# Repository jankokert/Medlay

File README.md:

# Medlay
A modular micropower managment layout

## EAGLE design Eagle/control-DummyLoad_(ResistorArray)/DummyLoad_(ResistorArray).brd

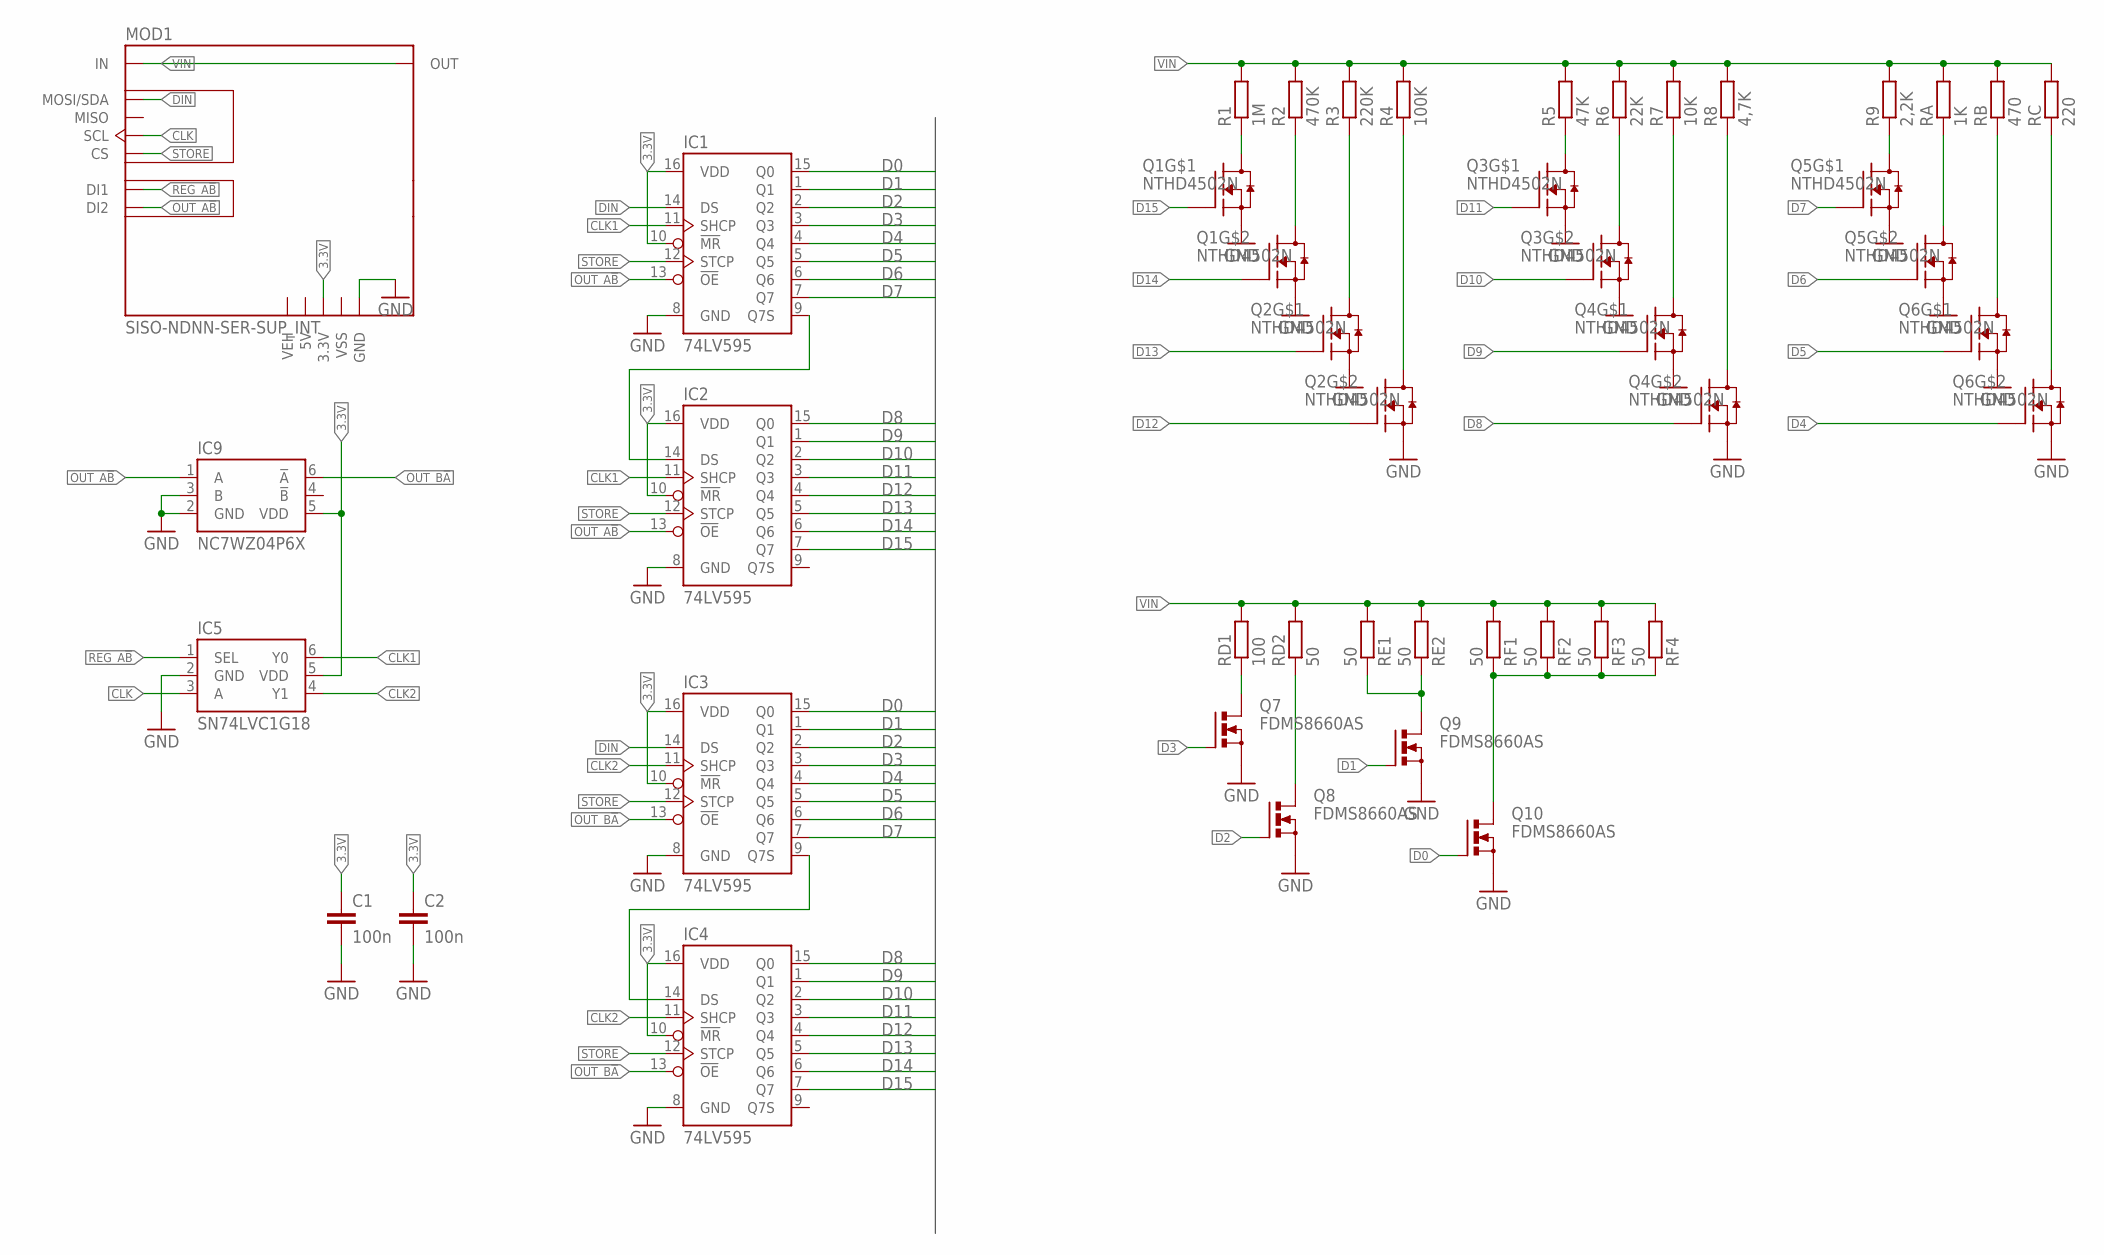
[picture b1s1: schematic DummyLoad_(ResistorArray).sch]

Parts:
C1, C2: 100n; C0805K
IC1, IC2, IC3, IC4: 74LV595; TSSOP16
IC5: SN74LVC1G18; SOT65
IC9: NC7WZ04P6X; SOT65P210X110-6N
MOD1: SISO-NDNN-SER-SUP_INT; SISO-NDNN-SER-SUP
Q1, Q2, Q3, Q4, Q5, Q6: NTHD4502N; 1206A_CHIPFET
Q7, Q8, Q9, Q10: FDMS8660AS; PG-TDSON-8
R1: 1M; R0805
R2: 470K; R0805
R3: 220K; R0805
R4: 100K; R0805
R5: 47K; R0805
R6: 22K; R0805
R7: 10K; R0805
R8: 4,7K; R0805
R9: 2,2K; R0805
RA: 1K; R0805
RB: 470; R0805
RC: 220; R0805
RD1: 100; R1206
RD2: 50; R1206
RE1, RE2: 50; R1206
RF1, RF2, RF3, RF4: 50; R1206

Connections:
3.3V: C1.1, C2.1, IC1.10 (!MR), IC1.16 (VDD), IC2.10 (!MR), IC2.16 (VDD), IC3.10 (!MR), IC3.16 (VDD), IC4.10 (!MR), IC4.16 (VDD), IC5.5 (VDD), IC9.5 (VDD), MOD1.3.3V
5V: MOD1.5V
CLK: IC5.3 (A), MOD1.SCL
CLK1: IC1.11 (SHCP), IC2.11 (SHCP), IC5.6 (Y0)
CLK2: IC3.11 (SHCP), IC4.11 (SHCP), IC5.4 (Y1)
D0: IC1.15 (Q0), IC3.15 (Q0), Q10.4 (G)
D1: IC1.1 (Q1), IC3.1 (Q1), Q9.4 (G)
D2: IC1.2 (Q2), IC3.2 (Q2), Q8.4 (G)
D3: IC1.3 (Q3), IC3.3 (Q3), Q7.4 (G)
D4: IC1.4 (Q4), IC3.4 (Q4), Q6.4 (G)
D5: IC1.5 (Q5), IC3.5 (Q5), Q6.2 (G)
D6: IC1.6 (Q6), IC3.6 (Q6), Q5.4 (G)
D7: IC1.7 (Q7), IC3.7 (Q7), Q5.2 (G)
D8: IC2.15 (Q0), IC4.15 (Q0), Q4.4 (G)
D9: IC2.1 (Q1), IC4.1 (Q1), Q4.2 (G)
D10: IC2.2 (Q2), IC4.2 (Q2), Q3.4 (G)
D11: IC2.3 (Q3), IC4.3 (Q3), Q3.2 (G)
D12: IC2.4 (Q4), IC4.4 (Q4), Q2.4 (G)
D13: IC2.5 (Q5), IC4.5 (Q5), Q2.2 (G)
D14: IC2.6 (Q6), IC4.6 (Q6), Q1.4 (G)
D15: IC2.7 (Q7), IC4.7 (Q7), Q1.2 (G)
DIN: IC1.14 (DS), IC3.14 (DS), MOD1.MOSI/SDA
GND: C1.2, C2.2, IC1.8 (GND), IC2.8 (GND), IC3.8 (GND), IC4.8 (GND), IC5.2 (GND), IC9.2 (GND), IC9.3 (B), MOD1.GND1 (GND), MOD1.GND2 (GND), MOD1.GND3 (GND), MOD1.GND4 (GND), Q1.1 (S), Q1.3 (S), Q2.1 (S), Q2.3 (S), Q3.1 (S), Q3.3 (S), Q4.1 (S), Q4.3 (S), Q5.1 (S), Q5.3 (S), Q6.1 (S), Q6.3 (S), Q7.1 (S), Q7.2 (S), Q7.3 (S), Q8.1 (S), Q8.2 (S), Q8.3 (S), Q9.1 (S), Q9.2 (S), Q9.3 (S), Q10.1 (S), Q10.2 (S), Q10.3 (S)
unnamed: Q7.5 (D), Q7.6 (D), Q7.7 (D), Q7.8 (D), Q7.TH (D), RD1.1
unnamed: Q1.7 (D), Q1.8 (D), R1.1
unnamed: IC1.9 (Q7S), IC2.14 (DS)
unnamed: IC3.9 (Q7S), IC4.14 (DS)
unnamed: Q5.7 (D), Q5.8 (D), R9.1
unnamed: Q5.5 (D), Q5.6 (D), RA.1
unnamed: Q6.7 (D), Q6.8 (D), RB.1
unnamed: Q6.5 (D), Q6.6 (D), RC.1
unnamed: Q1.5 (D), Q1.6 (D), R2.1
unnamed: Q2.7 (D), Q2.8 (D), R3.1
unnamed: Q8.5 (D), Q8.6 (D), Q8.7 (D), Q8.8 (D), Q8.TH (D), RD2.1
unnamed: Q2.5 (D), Q2.6 (D), R4.1
unnamed: Q3.7 (D), Q3.8 (D), R5.1
unnamed: Q9.5 (D), Q9.6 (D), Q9.7 (D), Q9.8 (D), Q9.TH (D), RE1.1, RE2.1
unnamed: Q3.5 (D), Q3.6 (D), R6.1
unnamed: Q4.7 (D), Q4.8 (D), R7.1
unnamed: Q4.5 (D), Q4.6 (D), R8.1
unnamed: Q10.5 (D), Q10.6 (D), Q10.7 (D), Q10.8 (D), Q10.TH (D), RF1.1, RF2.1, RF3.1, RF4.1
OUT_A!B: IC1.13 (!OE), IC2.13 (!OE), IC9.1 (A), MOD1.DI2
OUT_B!A: IC3.13 (!OE), IC4.13 (!OE), IC9.6 (!A)
REG_A!B: IC5.1 (SEL), MOD1.DI1
STORE: IC1.12 (STCP), IC2.12 (STCP), IC3.12 (STCP), IC4.12 (STCP), MOD1.CS
VEH: MOD1.VEH
VIN: MOD1.IN1 (IN), MOD1.IN2 (IN), MOD1.IN3 (IN), MOD1.IN4 (IN), MOD1.OUT1 (OUT), MOD1.OUT2 (OUT), MOD1.OUT3 (OUT), MOD1.OUT4 (OUT), R1.2, R2.2, R3.2, R4.2, R5.2, R6.2, R7.2, R8.2, R9.2, RA.2, RB.2, RC.2, RD1.2, RD2.2, RE1.2, RE2.2, RF1.2, RF2.2, RF3.2, RF4.2
VSS: MOD1.VSS

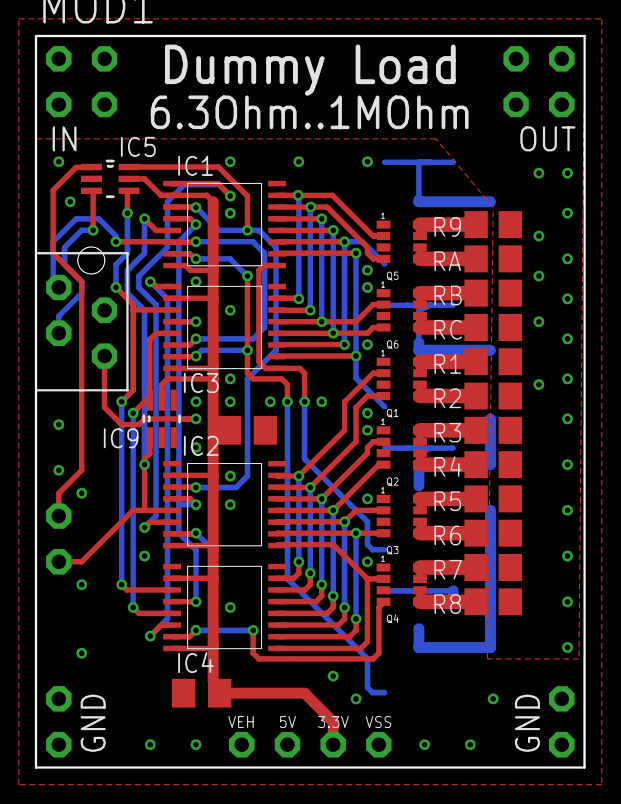
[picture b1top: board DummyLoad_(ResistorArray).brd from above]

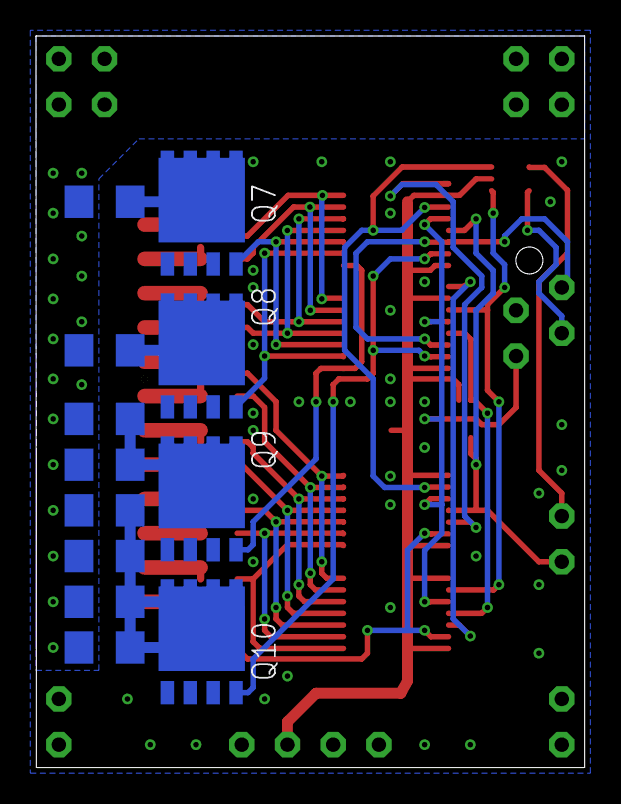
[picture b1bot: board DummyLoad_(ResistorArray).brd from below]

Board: 2 copper layers, 30.5 x 40.6 mm, 39 parts (12 on the bottom side), 45 nets.

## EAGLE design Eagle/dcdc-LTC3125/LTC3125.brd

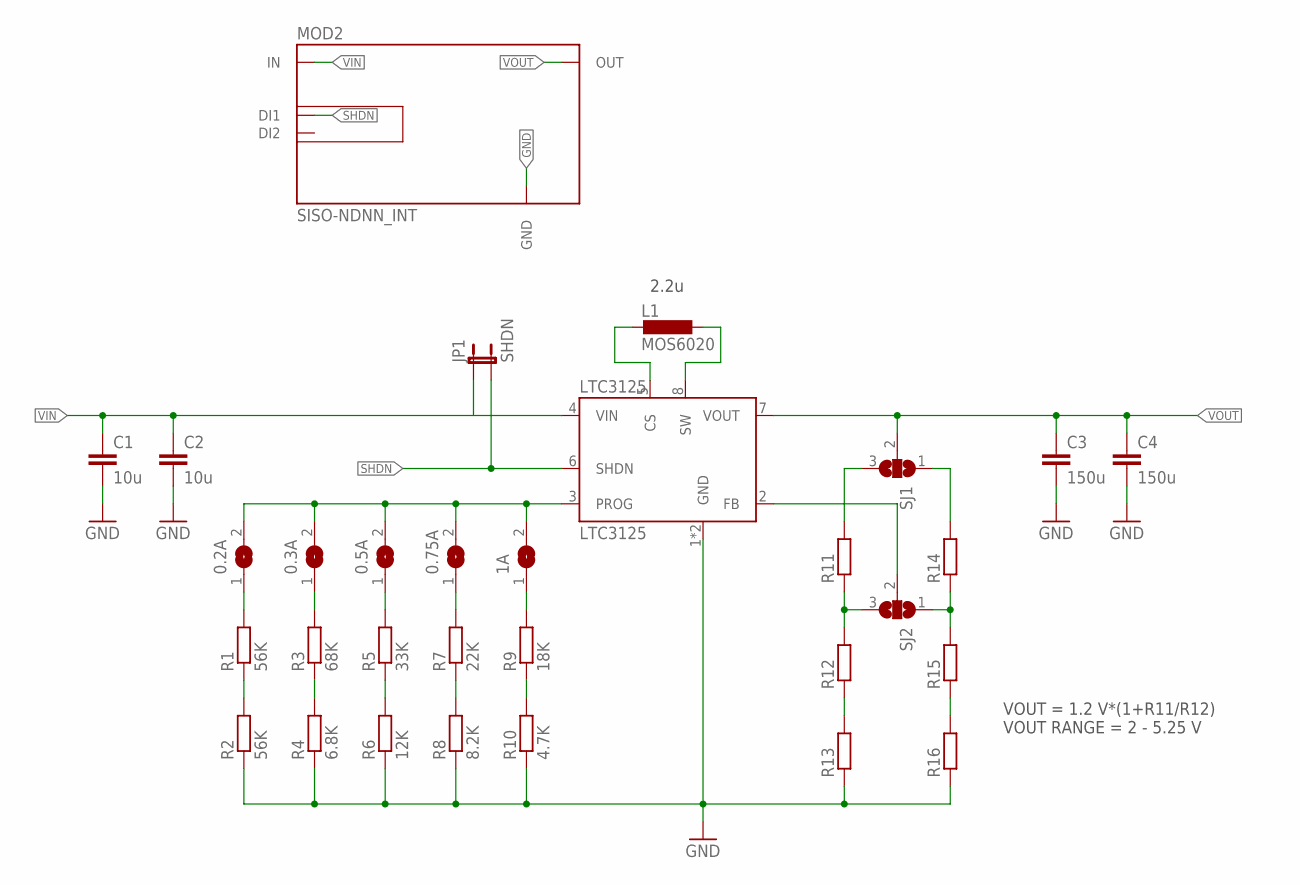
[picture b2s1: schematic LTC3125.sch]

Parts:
0.2A, 0.3A, 0.5A, 0.75A, 1A: SJ2
C1, C2: 10u; C0805
C3, C4: 150u; C0805
JP1: SHDN; JP2_SMALL_PAD
L1: MOS6020
LTC3125: LTC3125; DFN8-2X3
MOD2: SISO-NDNN_INT; SISO-NDNN
R1, R2: 56K; R0805
R3: 68K; R0805
R4: 6.8K; R0805
R5: 33K; R0805
R6: 12K; R0805
R7: 22K; R0805
R8: 8.2K; R0805
R9: 18K; R0805
R10: 4.7K; R0805
R11, R12, R13, R14, R15, R16: R-EU_R0805; R0805
SJ1, SJ2: SJ3

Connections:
GND: C1.2, C2.2, C3.2, C4.2, LTC3125.1 (GND), LTC3125.EXP (GND), MOD2.GND1 (GND), MOD2.GND2 (GND), MOD2.GND3 (GND), MOD2.GND4 (GND), R2.1, R4.1, R6.1, R8.1, R10.1, R13.1, R16.1
unnamed: 0.2A.2, 0.3A.2, 0.5A.2, 0.75A.2, 1A.2, LTC3125.3 (PROG)
unnamed: 0.2A.1, R1.2
unnamed: 0.3A.1, R3.2
unnamed: 0.5A.1, R5.2
unnamed: 0.75A.1, R7.2
unnamed: 1A.1, R9.2
unnamed: R1.1, R2.2
unnamed: R3.1, R4.2
unnamed: R5.1, R6.2
unnamed: L1.1, LTC3125.5 (CS)
unnamed: L1.2, LTC3125.8 (SW)
unnamed: R11.1, R12.2, SJ2.3
unnamed: R7.1, R8.2
unnamed: R9.1, R10.2
unnamed: R12.1, R13.2
unnamed: R11.2, SJ1.3
unnamed: LTC3125.2 (FB), SJ2.2
unnamed: R14.2, SJ1.1
unnamed: R14.1, R15.2, SJ2.1
unnamed: R15.1, R16.2
SHDN: JP1.2, LTC3125.6 (SHDN), MOD2.DI1
VIN: C1.1, C2.1, JP1.1, LTC3125.4 (VIN), MOD2.IN1 (IN), MOD2.IN2 (IN), MOD2.IN3 (IN), MOD2.IN4 (IN)
VOUT: C3.1, C4.1, LTC3125.7 (VOUT), MOD2.OUT1 (OUT), MOD2.OUT2 (OUT), MOD2.OUT3 (OUT), MOD2.OUT4 (OUT), SJ1.2

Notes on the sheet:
VOUT = 1.2 V*(1+R11/R12) VOUT RANGE = 2 - 5.25 V
2.2u

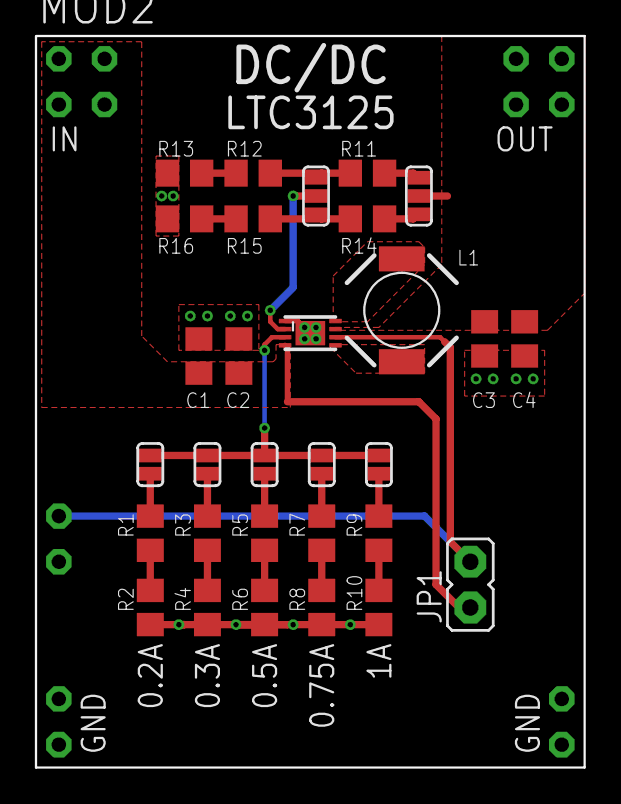
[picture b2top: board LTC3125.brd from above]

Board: 2 copper layers, 30.5 x 40.6 mm, 31 parts (0 on the bottom side), 24 nets.

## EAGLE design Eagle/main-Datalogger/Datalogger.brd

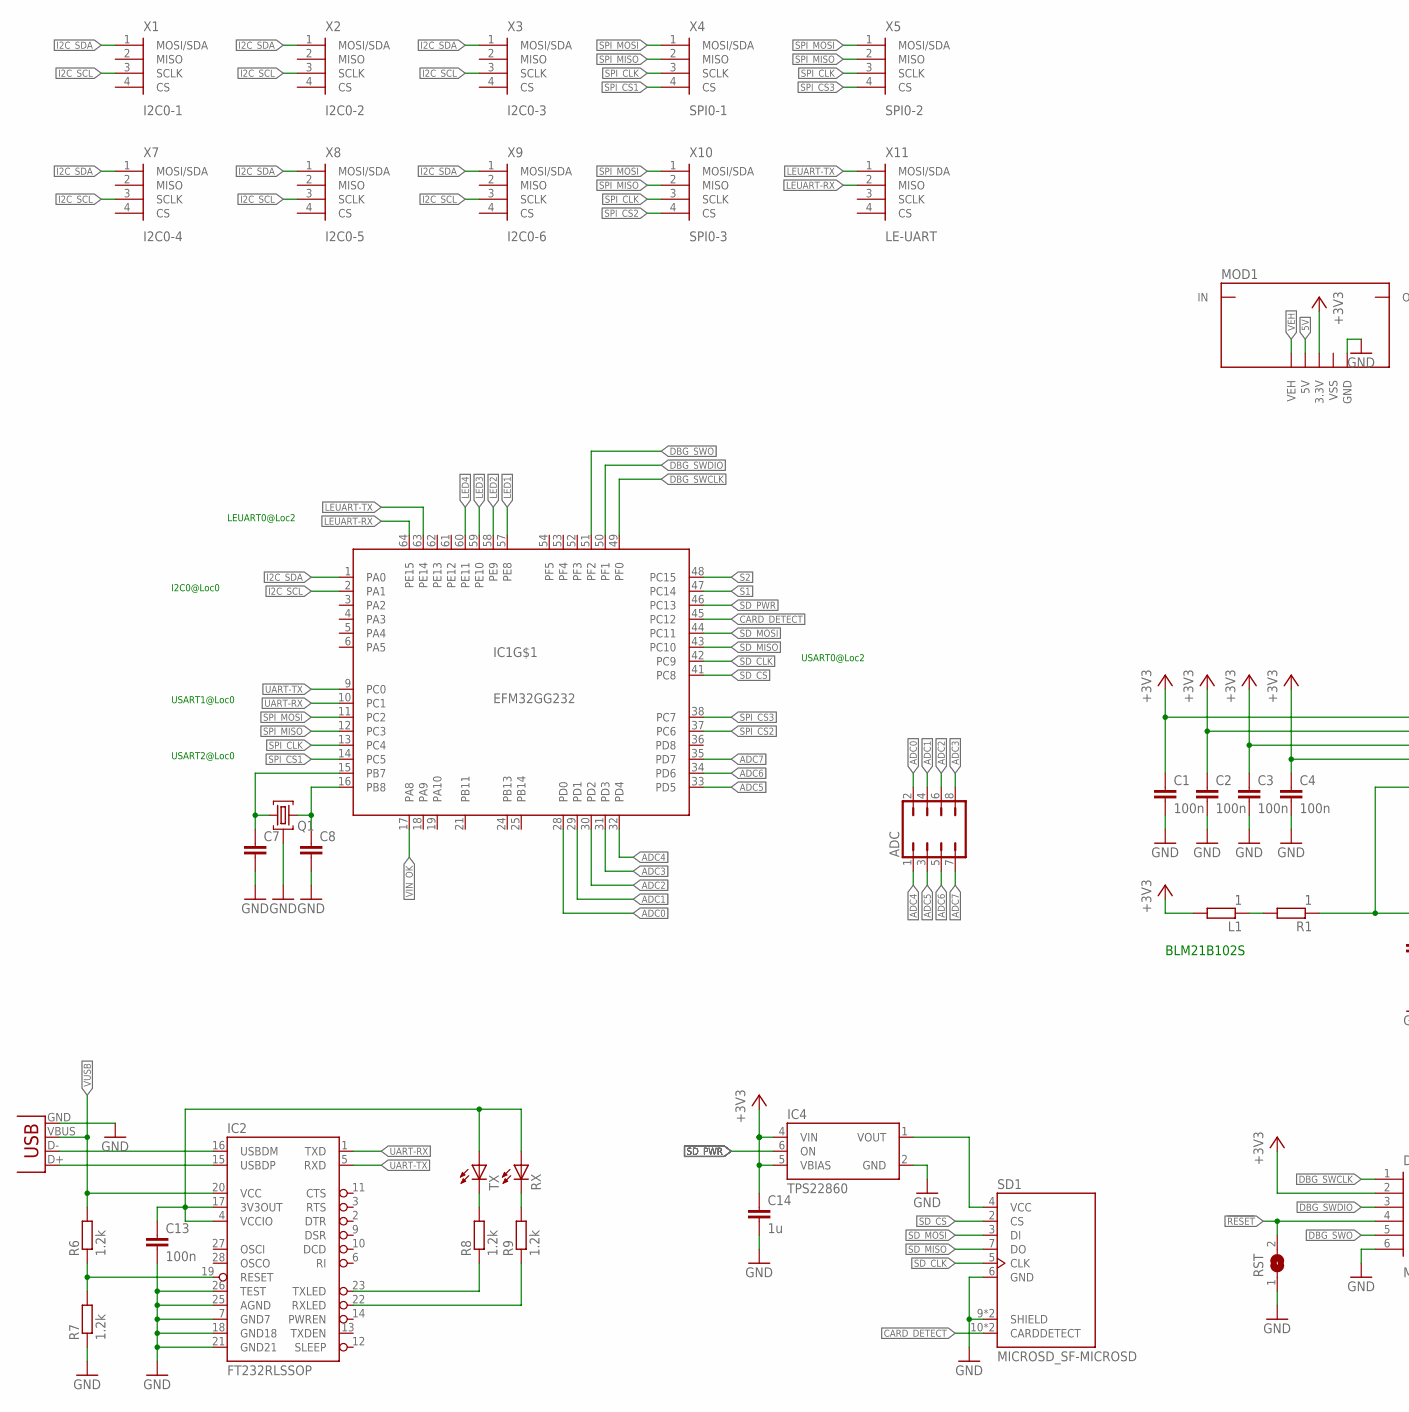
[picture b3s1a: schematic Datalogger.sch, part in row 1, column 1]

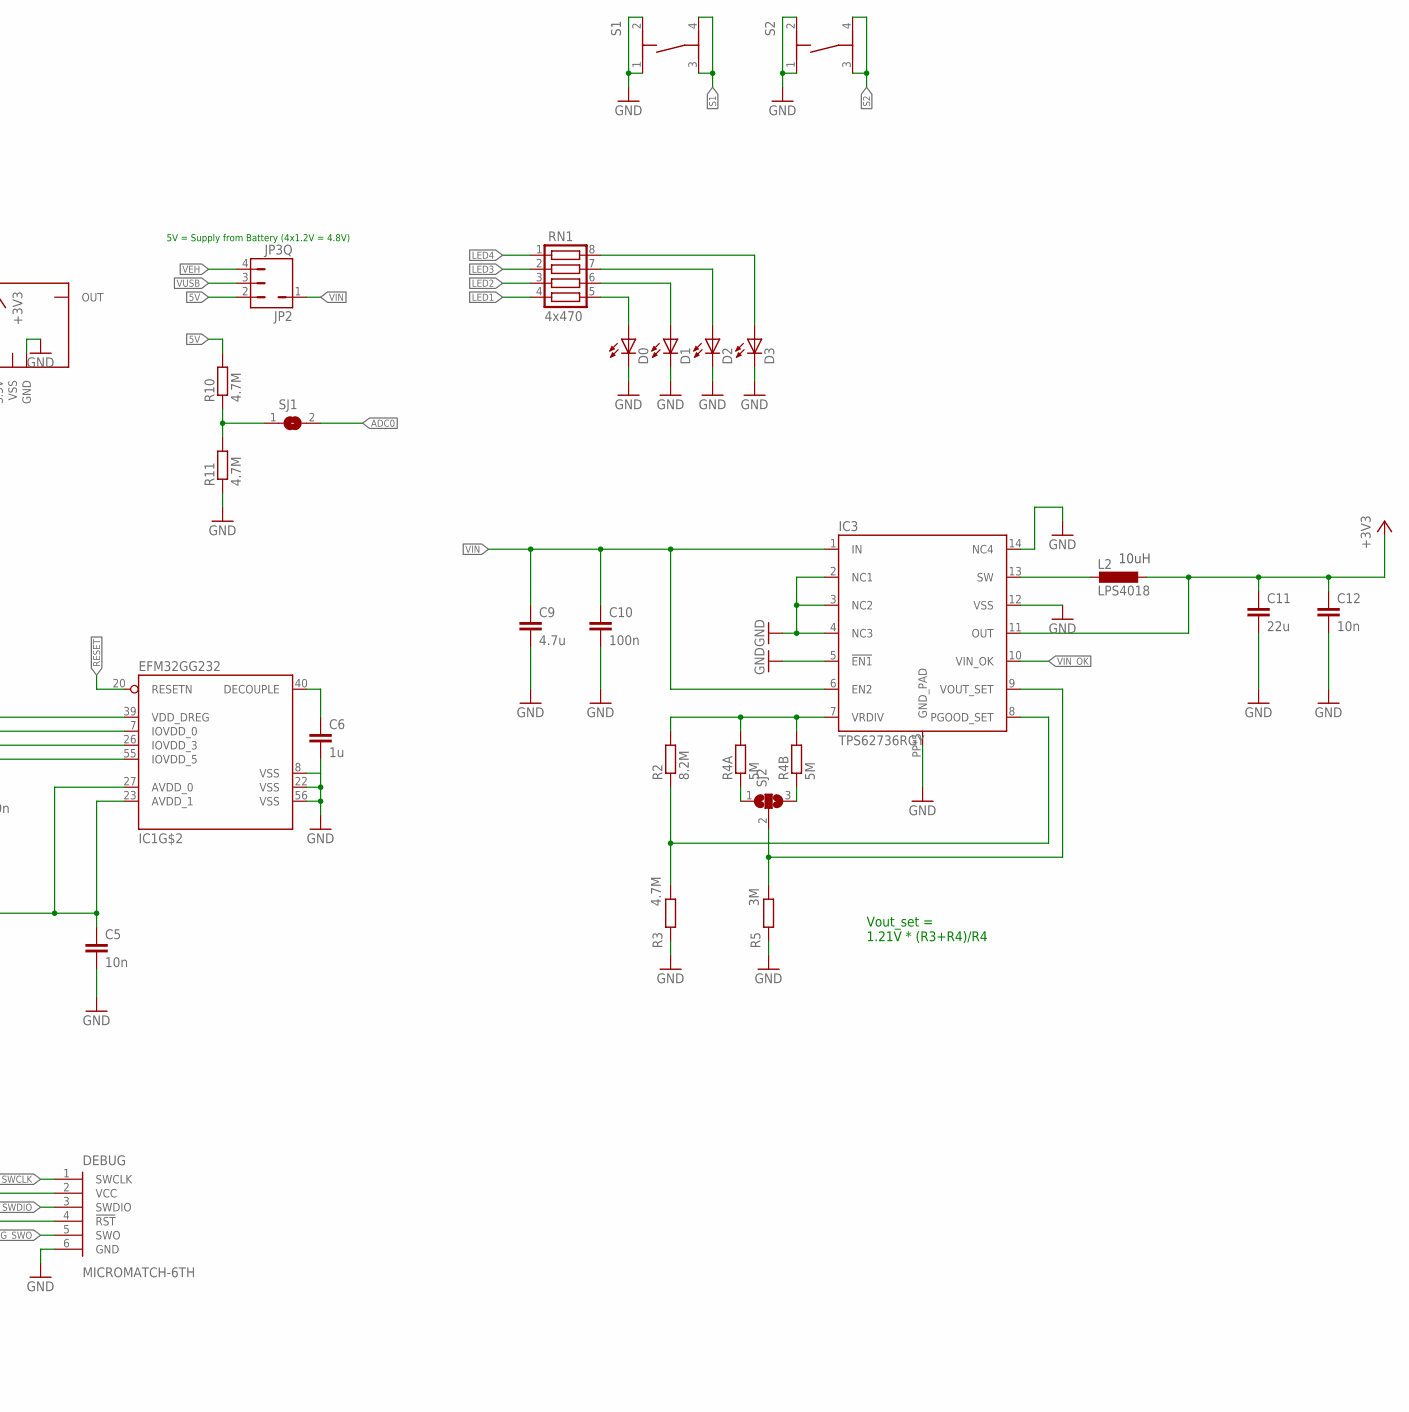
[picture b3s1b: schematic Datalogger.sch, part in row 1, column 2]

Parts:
ADC: JP2X4; JP4X2
C1, C2, C3, C4: 100n; C0603K
C5: 10n; C0603K
C6, C14: 1u; C0805K
C7, C8: C-EUC0603K; C0603K
C9: 4.7u; C0805
C10: 100n; C0805
C11: 22u; C0805
C12: 10n; C0805
C13: 100n; C0805K
D0, D1, D2, D3: LEDCHIPLED_0805; CHIPLED_0805
DEBUG: MICROMATCH-6TH; MICROMATCH-6
IC1: EFM32GG232; QFP64
IC2: FT232RLSSOP; SSOP28DB
IC3: TPS62736RGY; S-PVQFN-N14
IC4: TPS22860; SOT23-6
JP2: JP3Q; JP1-3
L1: 1; R0805
L2: LPS4018
MOD1: 2M-SISO_INT; 2M-SISO-NNNN-SUP
Q1: TC38H
R1: 1; R0805
R2: 8.2M; R0805
R3, R10, R11: 4.7M; R0805
R4A, R4B: 5M; R0805
R5: 3M; R0805
R6, R7, R8, R9: 1.2k; R0805
RN1: 4x470; CTS742C083
RST: SJ2
RX: LEDCHIPLED_0805; CHIPLED_0805
S1, S2: TASTER-9314_SMD
SD1: MICROSD_SF-MICROSD; MICROSD_MICROSD
SJ1: SJ2
SJ2: SJ3
TX: LEDCHIPLED_0805; CHIPLED_0805
X1: I2C0-1; MICROMATCH-4SMD
X2: I2C0-2; MICROMATCH-4SMD
X3: I2C0-3; MICROMATCH-4SMD
X4: SPI0-1; MICROMATCH-4SMD
X5: SPI0-2; MICROMATCH-4SMD
X7: I2C0-4; MICROMATCH-4SMD
X8: I2C0-5; MICROMATCH-4SMD
X9: I2C0-6; MICROMATCH-4SMD
X10: SPI0-3; MICROMATCH-4SMD
X11: LE-UART; MICROMATCH-4SMD
XUSB: USB-SMD-NS; USB-MINIB-NOSTOP

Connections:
5V: JP2.2, MOD1.5V, R10.2
!RESET: DEBUG.4 (!RST), IC1.20 (RESETN), RST.2
+3V3: C1.1, C2.1, C3.1, C4.1, C11.1, C12.1, C14.1, DEBUG.2 (VCC), IC1.7 (IOVDD_0), IC1.26 (IOVDD_3), IC1.39 (VDD_DREG), IC1.55 (IOVDD_5), IC3.11 (OUT), IC4.4 (VIN), IC4.5 (VBIAS), L1.2, L2.2, MOD1.3.3V
ADC0: ADC.2, IC1.28 (PD0), SJ1.2
ADC1: ADC.4, IC1.29 (PD1)
ADC2: ADC.6, IC1.30 (PD2)
ADC3: ADC.8, IC1.31 (PD3)
ADC4: ADC.1, IC1.32 (PD4)
ADC5: ADC.3, IC1.33 (PD5)
ADC6: ADC.5, IC1.34 (PD6)
ADC7: ADC.7, IC1.35 (PD7)
CARD_DETECT: IC1.45 (PC12), SD1.10 (CARDDETECT), SD1.10.2 (CARDDETECT)
DBG_SWCLK: DEBUG.1 (SWCLK), IC1.49 (PF0)
DBG_SWDIO: DEBUG.3 (SWDIO), IC1.50 (PF1)
DBG_SWO: DEBUG.5 (SWO), IC1.51 (PF2)
GND: C1.2, C2.2, C3.2, C4.2, C5.2, C6.2, C7.2, C8.2, C9.2, C10.2, C11.2, C12.2, C13.2, C14.2, D0.C, D1.C, D2.C, D3.C, DEBUG.6 (GND), IC1.8 (VSS), IC1.22 (VSS), IC1.56 (VSS), IC2.7 (GND7), IC2.18 (GND18), IC2.21 (GND21), IC2.25 (AGND), IC2.26 (TEST), IC3.2 (NC1), IC3.3 (NC2), IC3.4 (NC3), IC3.5 (!EN1), IC3.12 (VSS), IC3.14 (NC4), IC3.PP (GND_PAD), IC3.PP@1 (GND_PAD), IC3.PP@2 (GND_PAD), IC3.PP@3 (GND_PAD), IC3.PP@4 (GND_PAD), IC4.2 (GND), MOD1.GND1 (GND), MOD1.GND2 (GND), MOD1.GND3 (GND), MOD1.GND4 (GND), Q1.3, R3.1, R5.1, R7.1, R11.1, RST.1, S1.1, S1.2, S2.1, S2.2, SD1.6 (GND), SD1.9 (SHIELD), SD1.9.2 (SHIELD), XUSB.GND
I2C_SCL: IC1.2 (PA1), X1.3 (SCLK), X2.3 (SCLK), X3.3 (SCLK), X7.3 (SCLK), X8.3 (SCLK), X9.3 (SCLK)
I2C_SDA: IC1.1 (PA0), X1.1 (MOSI/SDA), X2.1 (MOSI/SDA), X3.1 (MOSI/SDA), X7.1 (MOSI/SDA), X8.1 (MOSI/SDA), X9.1 (MOSI/SDA)
LED1: IC1.57 (PE8), RN1.4
LED2: IC1.58 (PE9), RN1.3
LED3: IC1.59 (PE10), RN1.2
LED4: IC1.60 (PE11), RN1.1
LEUART-RX: IC1.64 (PE15), X11.2 (MISO)
LEUART-TX: IC1.63 (PE14), X11.1 (MOSI/SDA)
unnamed: IC2.16 (USBDM), XUSB.D-
unnamed: IC2.15 (USBDP), XUSB.D+
unnamed: L1.1, R1.2
unnamed: R8.2, TX.C
unnamed: IC2.19 (RESET), R6.1, R7.2
unnamed: C6.1, IC1.40 (DECOUPLE)
unnamed: R9.2, RX.C
unnamed: C7.1, IC1.15 (PB7), Q1.1
unnamed: IC2.23 (TXLED), R8.1
unnamed: IC2.22 (RXLED), R9.1
unnamed: R4A.1, SJ2.1
unnamed: C5.1, IC1.23 (AVDD_1), IC1.27 (AVDD_0), R1.1
unnamed: C8.1, IC1.16 (PB8), Q1.2
unnamed: IC4.1 (VOUT), SD1.4 (VCC)
unnamed: C13.1, IC2.4 (VCCIO), IC2.17 (3V3OUT), RX.A, TX.A
unnamed: R4B.1, SJ2.3
unnamed: IC3.13 (SW), L2.1
unnamed: IC3.7 (VRDIV), R2.2, R4A.2, R4B.2
unnamed: D0.A, RN1.5
unnamed: D1.A, RN1.6
unnamed: D2.A, RN1.7
unnamed: D3.A, RN1.8
unnamed: R10.1, R11.2, SJ1.1
PGOOD_SET: IC3.8 (PGOOD_SET), R2.1, R3.2
S1: IC1.47 (PC14), S1.3, S1.4
S2: IC1.48 (PC15), S2.3, S2.4
SD_CLK: IC1.42 (PC9), SD1.5 (CLK)
SD_CS: IC1.41 (PC8), SD1.2 (CS)
SD_MISO: IC1.43 (PC10), SD1.7 (DO)
SD_MOSI: IC1.44 (PC11), SD1.3 (DI)
SD_PWR: IC1.46 (PC13), IC4.6 (ON)
SPI_CLK: IC1.13 (PC4), X4.3 (SCLK), X5.3 (SCLK), X10.3 (SCLK)
SPI_CS1: IC1.14 (PC5), X4.4 (CS)
SPI_CS2: IC1.37 (PC6), X10.4 (CS)
SPI_CS3: IC1.38 (PC7), X5.4 (CS)
SPI_MISO: IC1.12 (PC3), X4.2 (MISO), X5.2 (MISO), X10.2 (MISO)
SPI_MOSI: IC1.11 (PC2), X4.1 (MOSI/SDA), X5.1 (MOSI/SDA), X10.1 (MOSI/SDA)
UART-RX: IC1.10 (PC1), IC2.1 (TXD)
UART-TX: IC1.9 (PC0), IC2.5 (RXD)
VEH: JP2.4, MOD1.VEH
VIN: C9.1, C10.1, IC3.1 (IN), IC3.6 (EN2), JP2.1
VIN_OK: IC1.17 (PA8), IC3.10 (VIN_OK)
VOUT_SET: IC3.9 (VOUT_SET), R5.2, SJ2.2
VSS: MOD1.VSS
VUSB: IC2.20 (VCC), JP2.3, R6.2, XUSB.VBUS

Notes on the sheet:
USART0@Loc2
LEUART0@Loc2
I2C0@Loc0
USART2@Loc0
USART1@Loc0
5V = Supply from Battery (4x1.2V = 4.8V)
BLM21B102S
10uH
Vout_set = 1.21V * (R3+R4)/R4

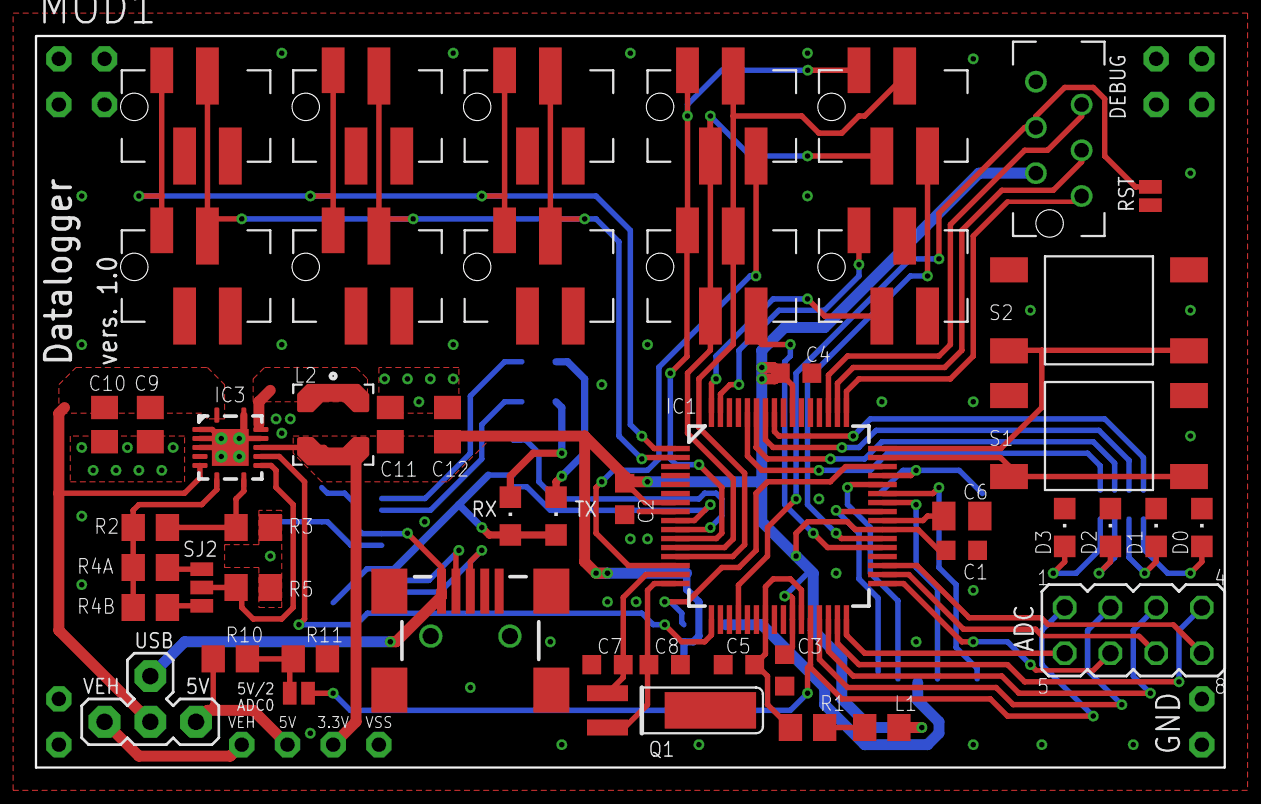
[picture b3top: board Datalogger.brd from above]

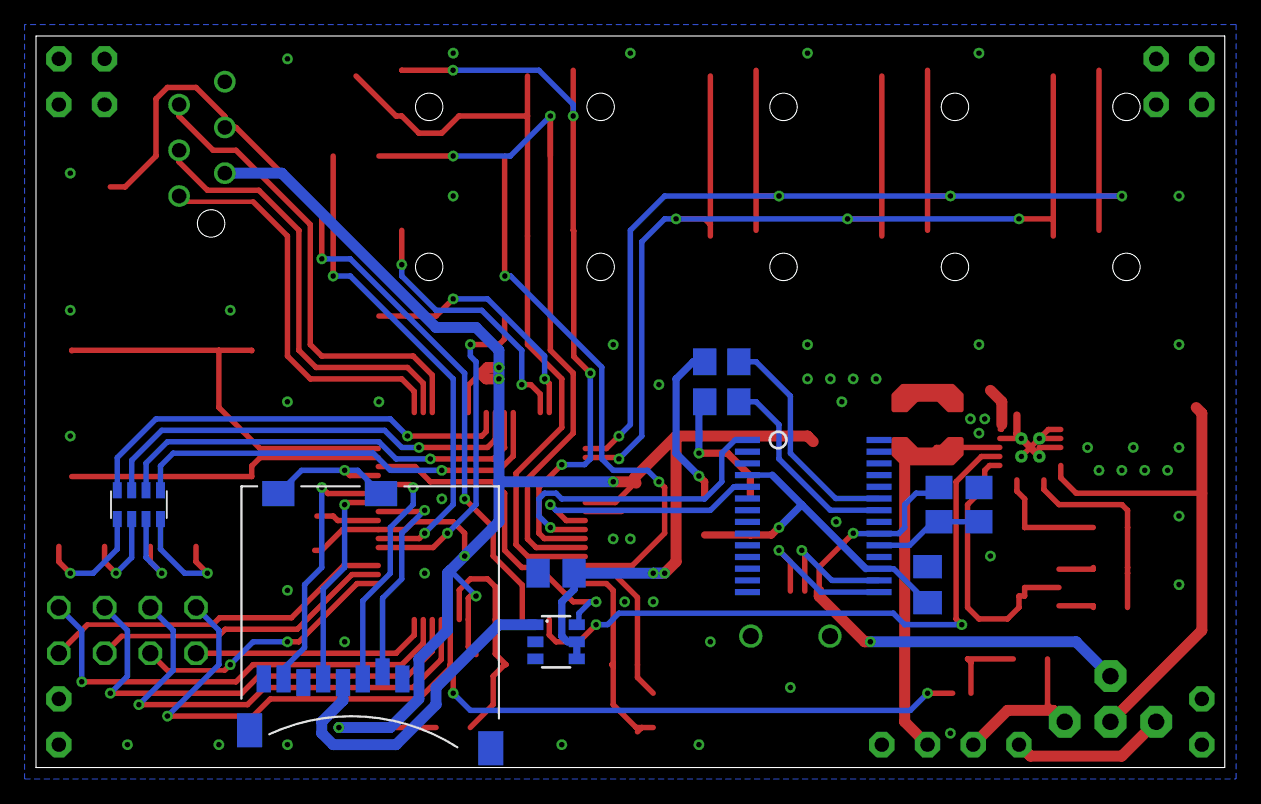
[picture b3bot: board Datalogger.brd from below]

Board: 2 copper layers, 66.0 x 40.6 mm, 61 parts (10 on the bottom side), 68 nets.

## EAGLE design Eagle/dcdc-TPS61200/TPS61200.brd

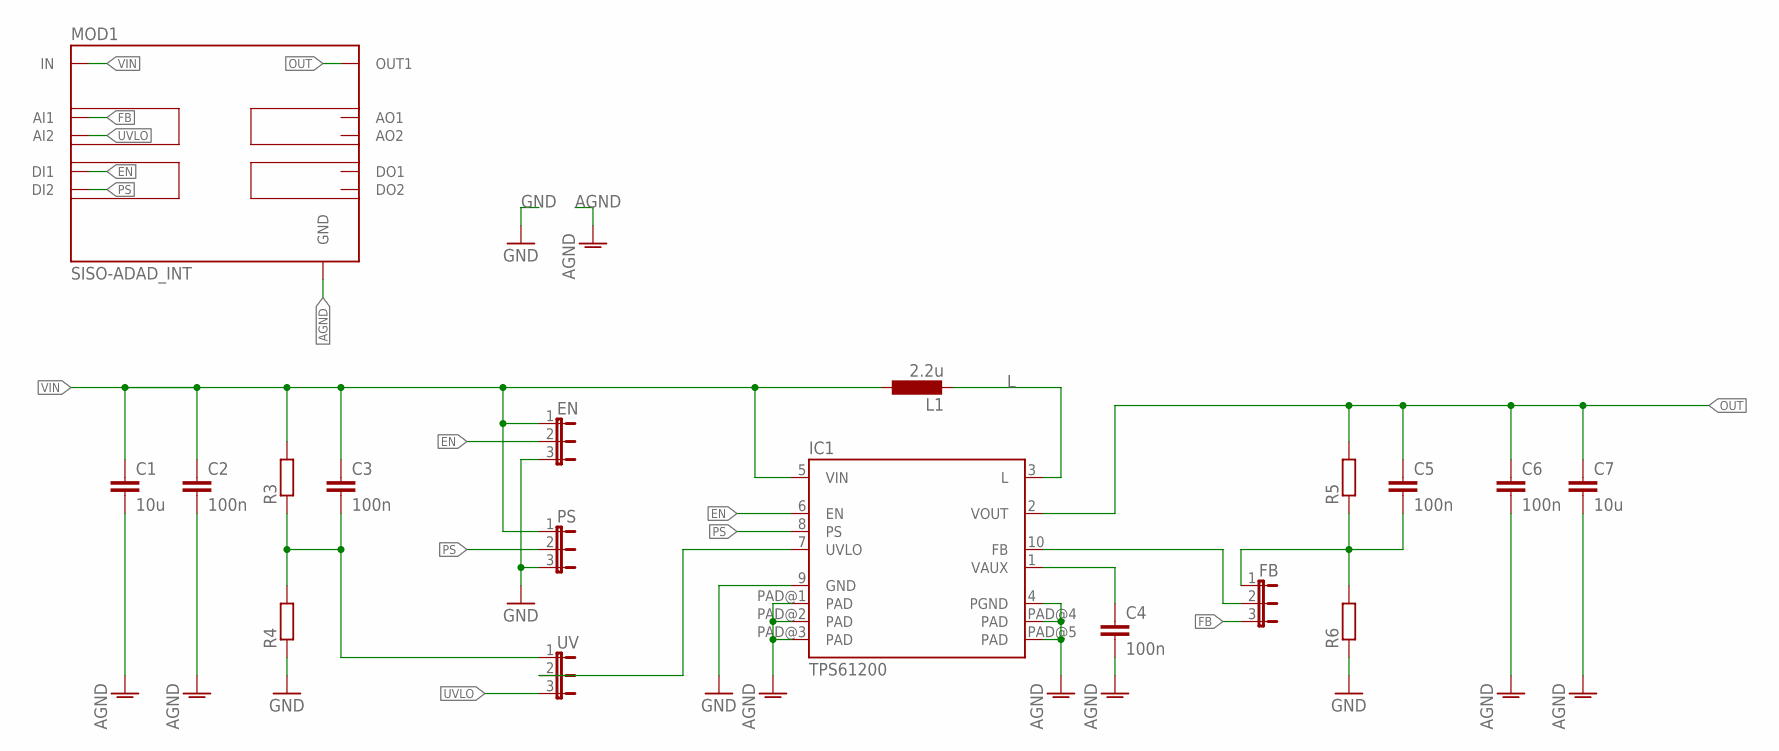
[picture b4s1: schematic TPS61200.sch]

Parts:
C1, C7: 10u; C0805
C2, C3, C4, C5, C6: 100n; C0805
EN: JP2E; JP2
FB: JP2E; JP2
IC1: TPS61200; QFN_10_PAD
L1: 2.2u; L4035M
MOD1: SISO-ADAD_INT; SISO-ADAD
PS: JP2E; JP2
R3, R4, R5, R6: R-EU_R0805; R0805
UV: JP2E; JP2

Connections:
AGND: C1.2, C2.2, C4.2, C6.2, C7.2, IC1.4 (PGND), IC1.PAD@1 (PAD), IC1.PAD@2 (PAD), IC1.PAD@3 (PAD), IC1.PAD@4 (PAD), IC1.PAD@5 (PAD), MOD1.GND1 (GND), MOD1.GND2 (GND), MOD1.GND3 (GND), MOD1.GND4 (GND)
EN: EN.2, IC1.6 (EN), MOD1.DI1
FB: FB.3, MOD1.AI1
GND: EN.3, IC1.9 (GND), PS.3, R4.1, R6.1
L: IC1.3 (L), L1.2
unnamed: IC1.7 (UVLO), UV.2
unnamed: C5.2, FB.1, R5.1, R6.2
unnamed: C3.2, R3.1, R4.2, UV.1
unnamed: C4.1, IC1.1 (VAUX)
unnamed: FB.2, IC1.10 (FB)
OUT: C5.1, C6.1, C7.1, IC1.2 (VOUT), MOD1.OUT1_1 (OUT1), MOD1.OUT1_2 (OUT1), MOD1.OUT1_3 (OUT1), MOD1.OUT1_4 (OUT1), R5.2
PS: IC1.8 (PS), MOD1.DI2, PS.2
UVLO: MOD1.AI2, UV.3
VIN: C1.1, C2.1, C3.1, EN.1, IC1.5 (VIN), L1.1, MOD1.IN1 (IN), MOD1.IN2 (IN), MOD1.IN3 (IN), MOD1.IN4 (IN), PS.1, R3.2

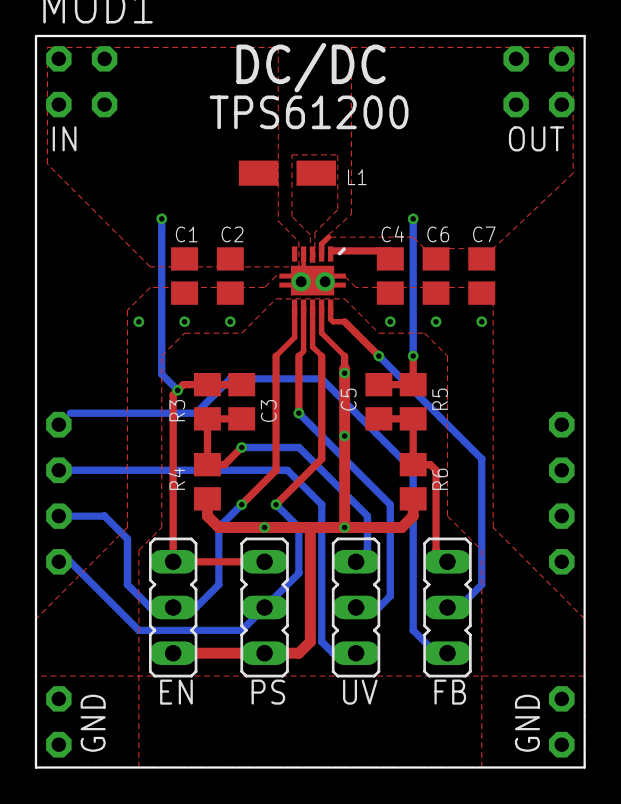
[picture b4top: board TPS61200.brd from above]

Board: 2 copper layers, 30.5 x 40.6 mm, 18 parts (0 on the bottom side), 14 nets.

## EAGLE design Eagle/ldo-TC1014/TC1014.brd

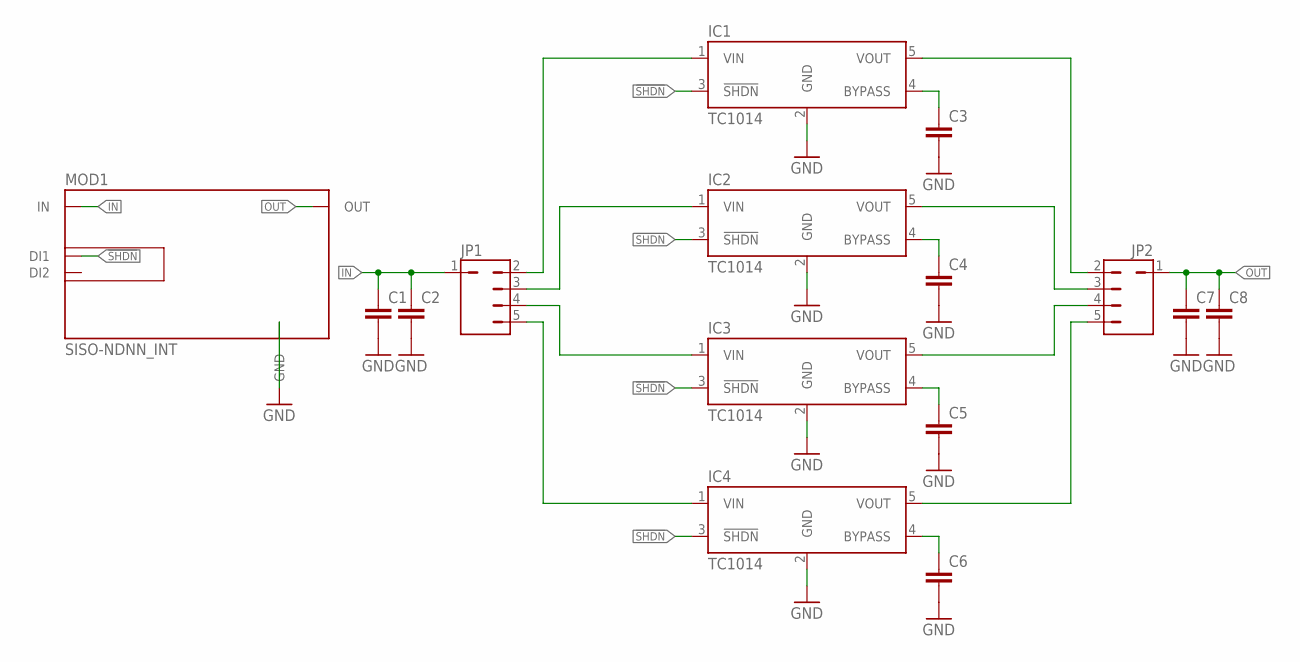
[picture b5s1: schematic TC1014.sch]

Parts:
C1, C2, C3, C4, C5, C6, C7, C8: C-EUC0805; C0805
IC1, IC2, IC3, IC4: TC1014; SOT23-5
JP1, JP2: JP4Q; JP1-4
MOD1: SISO-NDNN_INT; SISO-NDNN

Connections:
!SHDN: IC1.3 (!SHDN), IC2.3 (!SHDN), IC3.3 (!SHDN), IC4.3 (!SHDN), MOD1.DI1
GND: C1.2, C2.2, C3.2, C4.2, C5.2, C6.2, C7.2, C8.2, IC1.2 (GND), IC2.2 (GND), IC3.2 (GND), IC4.2 (GND), MOD1.GND1 (GND), MOD1.GND2 (GND), MOD1.GND3 (GND), MOD1.GND4 (GND)
IN: C1.1, C2.1, JP1.1, MOD1.IN1 (IN), MOD1.IN2 (IN), MOD1.IN3 (IN), MOD1.IN4 (IN)
unnamed: IC1.1 (VIN), JP1.2
unnamed: IC2.1 (VIN), JP1.3
unnamed: IC3.1 (VIN), JP1.4
unnamed: IC4.1 (VIN), JP1.5
unnamed: IC1.5 (VOUT), JP2.2
unnamed: IC2.5 (VOUT), JP2.3
unnamed: IC3.5 (VOUT), JP2.4
unnamed: IC4.5 (VOUT), JP2.5
unnamed: C3.1, IC1.4 (BYPASS)
unnamed: C4.1, IC2.4 (BYPASS)
unnamed: C5.1, IC3.4 (BYPASS)
unnamed: C6.1, IC4.4 (BYPASS)
OUT: C7.1, C8.1, JP2.1, MOD1.OUT1 (OUT), MOD1.OUT2 (OUT), MOD1.OUT3 (OUT), MOD1.OUT4 (OUT)

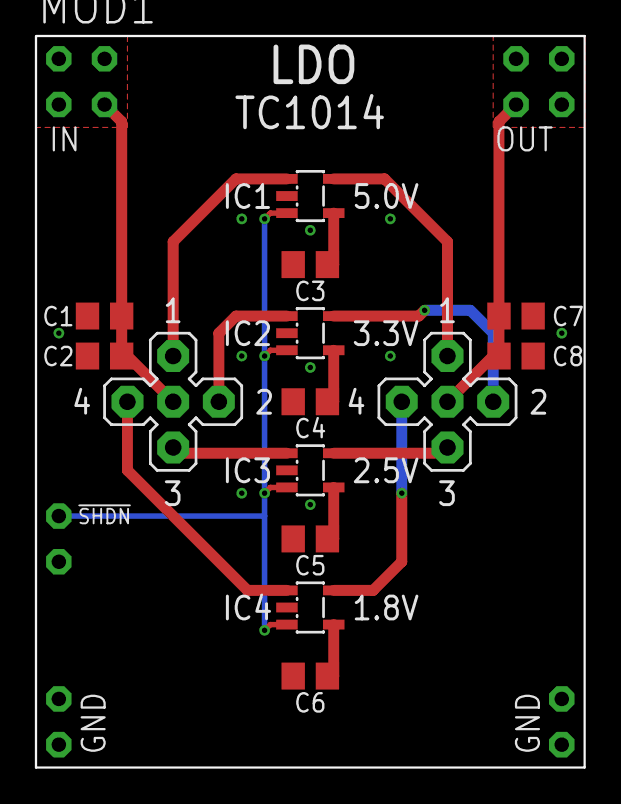
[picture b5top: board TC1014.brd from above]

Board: 2 copper layers, 30.5 x 40.6 mm, 15 parts (0 on the bottom side), 16 nets.
